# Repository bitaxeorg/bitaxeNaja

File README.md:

BitaxeNaja is a dual BM1373 Open Source Bitcoin miner using [esp-miner](https://github.com/skot/esp-miner)

The BM1373 used in this design is suspected to be the ASIC used in the Antminer S23 series miners.

It is still an untested prototype! Don't build this expecting it to work at all.

Bitaxe is an open source project released under the [CERN Open Hardware Licence Version 2 - Strongly Reciprocal](LICENSE)

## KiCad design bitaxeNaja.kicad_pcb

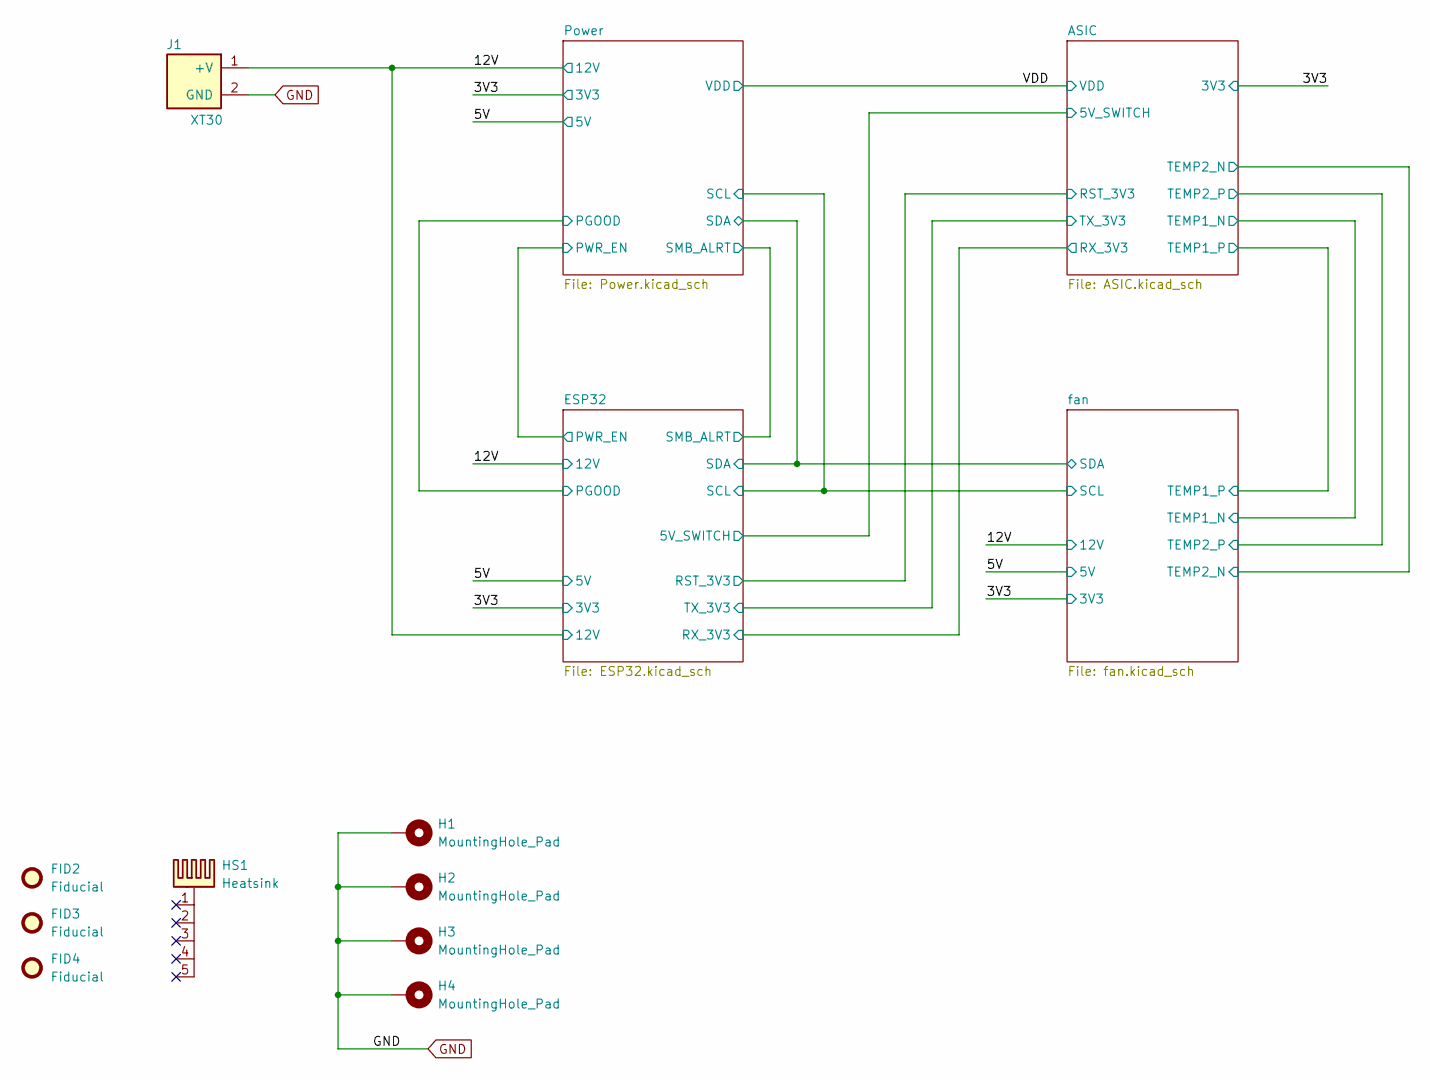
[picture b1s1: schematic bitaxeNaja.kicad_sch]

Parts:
FID2, FID3, FID4: Fiducial; Fiducial_1mm_Mask2mm
H1, H2, H3, H4: MountingHole_Pad; MountingHole_3.2mm_M3_Pad_Via
HS1: Heatsink; Heatsink-5hole-BitaxeGT
J1: XT30; XT30PW-M; PARTNO XT30PW-M; LCSC C431092

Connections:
/12V: J1.1 (+V); also elsewhere on the board
GND: H1.1 (1_1), H2.1 (1_1), H3.1 (1_1), H4.1 (1_1), J1.2 (GND); also elsewhere on the board

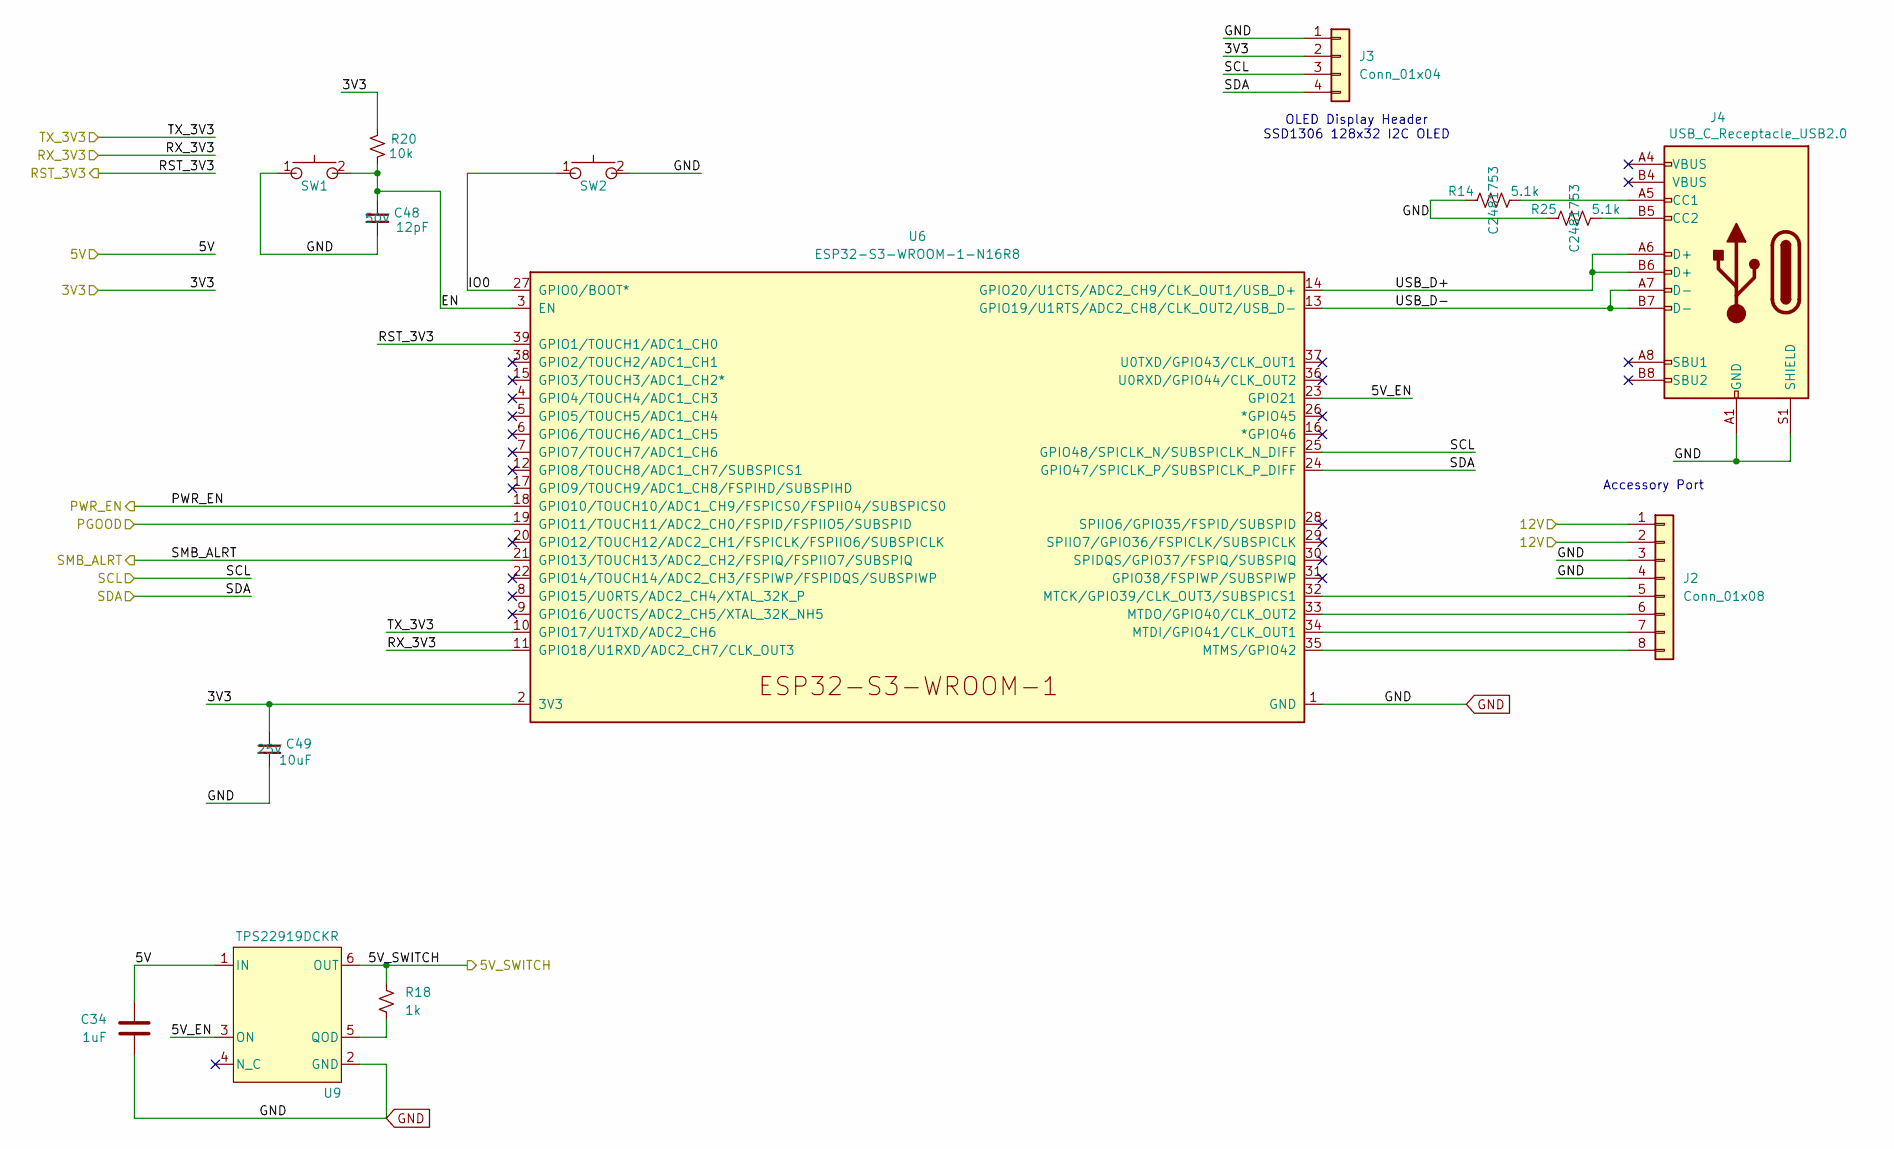
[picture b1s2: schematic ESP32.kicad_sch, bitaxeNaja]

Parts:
C34: 1uF; C_0402_1005Metric; PARTNO EMK105BJ105MV-F; LCSC C2177690
C48: 12pF; C_0402_1005Metric; Voltage 50V; PARTNO CC0402JRNPO9BN120
C49: 10uF; C_0603_1608Metric; Voltage 25V; PARTNO GRM188R61E106KA73D; LCSC C344022
J2: Conn_01x08; FPC-SMD_P0.50-8P_FGS-XJ-H2.0; PARTNO FFC2B35-08-T; LCSC C262657
J3: Conn_01x04; PinHeader_1x04_P2.54mm_Vertical_shifted
J4: USB_C_Receptacle_USB2.0; USB_C_Receptacle_GCT_USB4105-xx-A; PARTNO USB4105-GF-A
R14, R25: 5.1k; R_0402_1005Metric; PARTNO RMCF0402JT5K10; LCSC C2481753
R18: 1k; R_0402_1005Metric; PARTNO RC0402FR-071KL
R20: 10k; R_0402_1005Metric; PARTNO RC0402JR-0710KL; LCSC C25744
SW1, SW2: SWITCH-SPST; SW_TL3330AF130QG_EWI; PARTNO TL3330AF130QG
U6: ESP32-S3-WROOM-1-N16R8; ESP32-S3-WROOM-1; PARTNO ESP32-S3-WROOM-1-N16R8
U9: TPS22919DCKR; DCK0006A_N; PARTNO TPS22919DCKR

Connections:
/3V3: C49.1, J3.2, R20.2, U6.2 (3V3); also elsewhere on the board
/5V: C34.1, U9.1 (IN); also elsewhere on the board
/12V: J2.1, J2.2; also elsewhere on the board
/ASIC/5V_SWITCH: R18.1, U9.6 (OUT); also elsewhere on the board
/ASIC/RST_3V3: U6.39 (GPIO1/TOUCH1/ADC1_CH0); also elsewhere on the board
/ASIC/RX_3V3: U6.11 (GPIO18/U1RXD/ADC2_CH7/CLK_OUT3); also elsewhere on the board
/ASIC/TX_3V3: U6.10 (GPIO17/U1TXD/ADC2_CH6); also elsewhere on the board
/ESP32/5V_EN: U6.23 (GPIO21), U9.3 (ON)
/ESP32/EN: C48.1, R20.1, SW1.2, U6.3 (EN)
/ESP32/IO0: SW2.1, U6.27 (GPIO0/BOOT*)
/ESP32/PWR_EN: U6.18 (GPIO10/TOUCH10/ADC1_CH9/FSPICS0/FSPIIO4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); also elsewhere on the board
/ESP32/SCL: J3.3, U6.25 (GPIO48/SPICLK_N/SUBSPICLK_N_DIFF); also elsewhere on the board
/ESP32/SDA: J3.4, U6.24 (GPIO47/SPICLK_P/SUBSPICLK_P_DIFF); also elsewhere on the board
/ESP32/SMB_ALRT: U6.21 (GPIO13/TOUCH13/ADC2_CH2/FSPIQ/FSPIIO7/S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); also elsewhere on the board
/ESP32/USB_D+: J4.A6 (D+), J4.B6 (D+), U6.14 (GPIO20/U1CTS/ADC2_CH9/CLK_OUT1/USB_D+)
/ESP32/USB_D-: J4.A7 (D-), J4.B7 (D-), U6.13 (GPIO19/U1RTS/ADC2_CH8/CLK_OUT2/USB_D-)
/Power/PGOOD: U6.19 (GPIO11/TOUCH11/ADC2_CH0/FSPID/FSPIIO5/S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); also elsewhere on the board
GND: C34.2, C48.2, C49.2, J2.3, J2.4, J3.1, J4.A1 (GND), J4.B1 (GND), J4.S1 (SHIELD), R14.1, R25.1, SW1.1, SW2.2, U6.1 (GND), U6.40 (GND), U6.41 (GND), U9.2 (GND); also elsewhere on the board
unnamed: J2.5, U6.32 (MTCK/GPIO39/CLK_OUT3/SUBSPICS1)
unnamed: J2.6, U6.33 (MTDO/GPIO40/CLK_OUT2)
unnamed: J2.7, U6.34 (MTDI/GPIO41/CLK_OUT1)
unnamed: J2.8, U6.35 (MTMS/GPIO42)
unnamed: J4.A5 (CC1), R14.2
unnamed: J4.B5 (CC2), R25.2
unnamed: R18.2, U9.5 (QOD)

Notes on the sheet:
OLED Display Header SSD1306 128x32 I2C OLED
Accessory Port

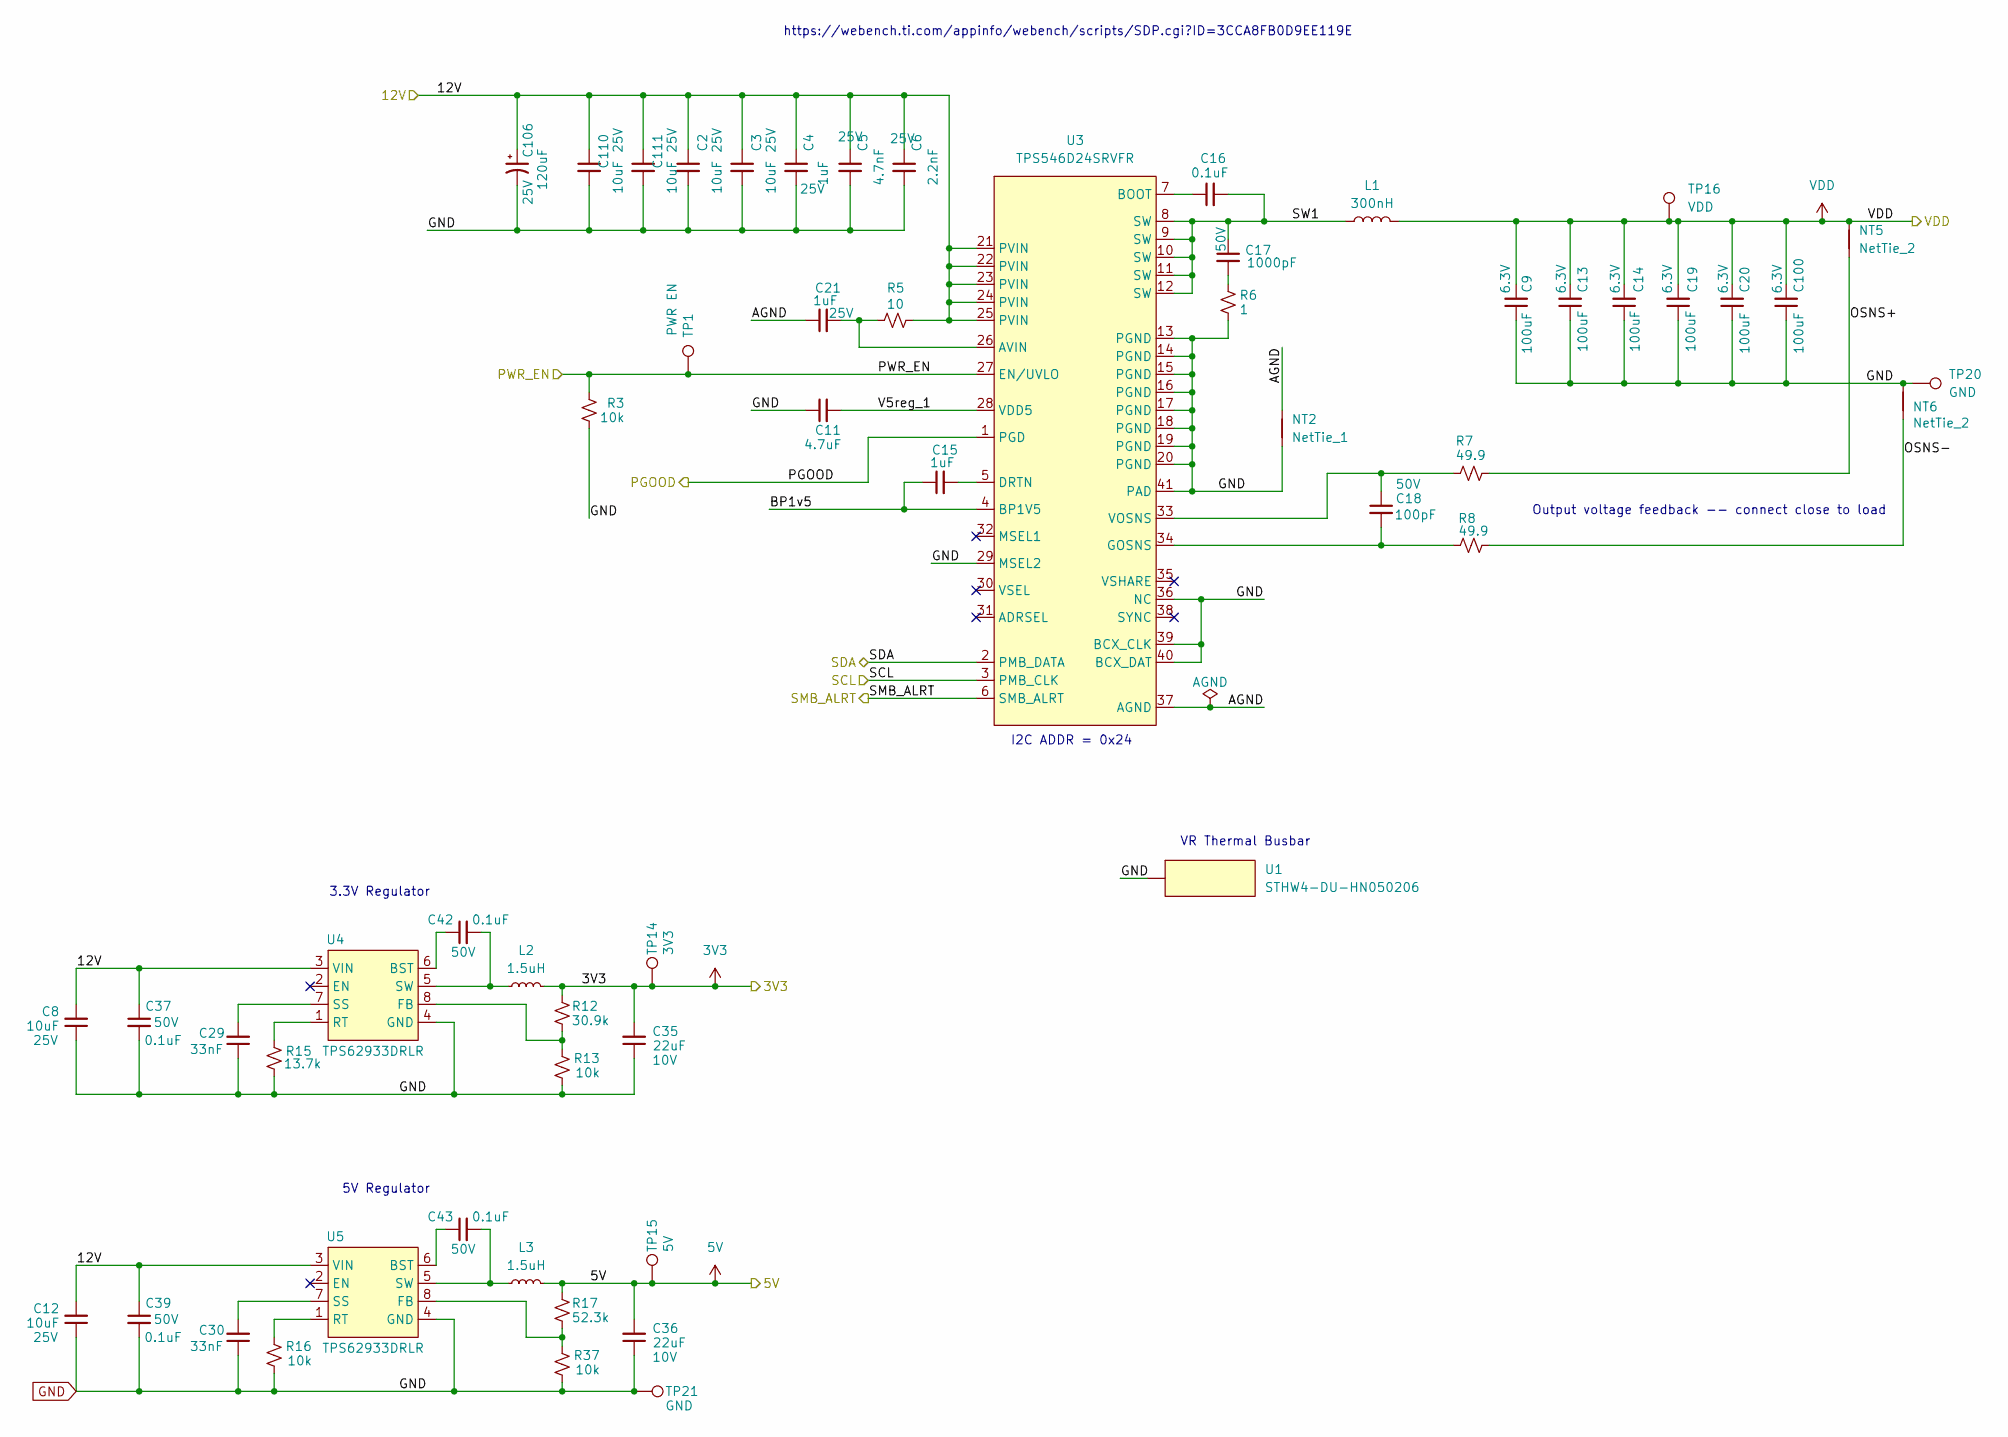
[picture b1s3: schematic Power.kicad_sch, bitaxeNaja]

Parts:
C2, C3, C8, C12, C110, C111: 10uF; C_0603_1608Metric; Voltage 25V; PARTNO GRM188R61E106KA73D; LCSC C344022
C4, C21: 1uF; C_0402_1005Metric; Voltage 25V; PARTNO TMK107B7105KA-T
C5: 4.7nF; C_0402_1005Metric; Voltage 25V; PARTNO GRM155R71E472KA01D
C6: 2.2nF; C_0402_1005Metric; Voltage 25V; PARTNO GRM155R61H222KA01D
C9, C13, C14, C19, C20, C100: 100uF; C_1206_3216Metric; Voltage 6.3V; PARTNO CL31A107MQHNNNE
C11: 4.7uF; C_0402_1005Metric; PARTNO GRM155R61A475MEAAD
C15: 1uF; C_0402_1005Metric; PARTNO EMK105BJ105MV-F; LCSC C2177690
C16, C37, C39, C42, C43: 0.1uF; C_0402_1005Metric; Voltage 50V; PARTNO GRM155R71H104KE14D; LCSC C77020
C17: 1000pF; C_0805_2012Metric; Voltage 50V; PARTNO CC0805KRX7R9BB102
C18: 100pF; C_0402_1005Metric; Voltage 50V; PARTNO CC0402JRNPO9BN101
C29, C30: 33nF; C_0402_1005Metric; PARTNO CC0402KRX7R9BB333; LCSC C106862
C35, C36: 22uF; C_0805_2012Metric; Voltage 10V; PARTNO CL21A226MPQNNNE; LCSC C29277
C106: 120uF; CP_Elec_6.3x5.9; Voltage 25V
L1: 300nH; SLC1175-271MEC_COC; PARTNO SLC1175-301
L2, L3: 1.5uH; IND-SMD_L2.0-W1.6; PARTNO FTC201612S1R5MBCA; LCSC C5832350
NT2: NetTie_1; NetTie-2_SMD_Pad0.2mmx1mm
NT5, NT6: NetTie_2; NetTie-2_SMD_Pad0.2mmx1mm
R3, R13, R16, R37: 10k; R_0402_1005Metric; PARTNO RC0402JR-0710KL; LCSC C25744
R5: 10; R_0402_1005Metric; PARTNO RC0402FR-0710RL
R6: 1; R_0805_2012Metric; PARTNO ESR10EZPJ1R0
R7, R8: 49.9; R_0402_1005Metric; PARTNO RC0402FR-0749R9L
R12: 30.9k; R_0402_1005Metric; PARTNO RC0402FR-0730K9L; LCSC C185428
R15: 13.7k; R_0402_1005Metric; PARTNO RC0402FR-0713K7L; LCSC C274888
R17: 52.3k; R_0402_1005Metric; PARTNO RC0402FR-0752K3L
TP1: PWR EN; TestPoint_Pad_D1.0mm
TP14: 3V3; TestPoint_Pad_D1.0mm
TP15: 5V; TestPoint_Pad_D1.0mm
TP16: VDD; TestPoint_Pad_D1.0mm
TP20: GND; TestPoint_Pad_D1.0mm
TP21: GND; TestPoint_Pad_D1.0mm; LCSC C138021
U1: STHW4-DU-HN050206; PAD-SMD_L5.0-W2.0_STHW4-DU-HN050206; LCSC C18548300
U3: TPS546D24SRVFR; LQFN40-CLIP; PARTNO TPS546D24SRVFR
U4, U5: TPS62933DRLR; SOT-583-8_L2.1-W1.2-P0.50-LS1.6-BR; PARTNO TPS62933DRLR; LCSC C3200405

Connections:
/3V3: C35.2, L2.2, R12.2, TP14.1 (1_1); also elsewhere on the board
/5V: C36.2, L3.2, R17.2, TP15.1 (1_1); also elsewhere on the board
/12V: C2.1, C3.1, C4.1, C5.1, C6.1, C8.2, C12.2, C37.1, C39.1, C106.1, C110.1, C111.1, R5.1, U3.21 (PVIN), U3.22 (PVIN), U3.23 (PVIN), U3.24 (PVIN), U3.25 (PVIN), U4.3 (VIN), U5.3 (VIN); also elsewhere on the board
/ESP32/PWR_EN: R3.2, TP1.1 (1_1), U3.27 (EN/UVLO); also elsewhere on the board
/ESP32/SCL: U3.3 (PMB_CLK); also elsewhere on the board
/ESP32/SDA: U3.2 (PMB_DATA); also elsewhere on the board
/ESP32/SMB_ALRT: U3.6 (SMB_ALRT); also elsewhere on the board
/Power/AGND: C21.1, NT2.2, U3.37 (AGND)
/Power/BP1v5: C15.1, U3.4 (BP1V5)
/Power/OSNS+: NT5.1, R7.1
/Power/OSNS-: NT6.1, R8.2
/Power/PGOOD: U3.1 (PGD); also elsewhere on the board
/Power/SW1: C16.2, C17.1, L1.1, U3.8 (SW), U3.9 (SW), U3.10 (SW), U3.11 (SW), U3.12 (SW)
/Power/V5reg_1: C11.2, U3.28 (VDD5)
/VDD: C9.2, C13.2, C14.2, C19.2, C20.2, C100.2, L1.2, NT5.2, TP16.1 (1_1); also elsewhere on the board
GND: C2.2, C3.2, C4.2, C5.2, C6.2, C8.1, C9.1, C11.1, C12.1, C13.1, C14.1, C19.1, C20.1, C29.1, C30.1, C35.1, C36.1, C37.2, C39.2, C100.1, C106.2, C110.2, C111.2, NT2.1, NT6.2, R3.1, R6.2, R13.1, R15.1, R16.1, R37.1, TP20.1 (1_1), TP21.1 (1_1), U1.1, U3.13 (PGND), U3.14 (PGND), U3.15 (PGND), U3.16 (PGND), U3.17 (PGND), U3.18 (PGND), U3.19 (PGND), U3.20 (PGND), U3.29 (MSEL2), U3.36 (NC), U3.39 (BCX_CLK), U3.40 (BCX_DAT), U3.41 (PAD), U4.4 (GND), U5.4 (GND); also elsewhere on the board
unnamed: C17.2, R6.1
unnamed: C21.2, R5.2, U3.26 (AVIN)
unnamed: C16.1, U3.7 (BOOT)
unnamed: C15.2, U3.5 (DRTN)
unnamed: C18.2, R8.1, U3.34 (GOSNS)
unnamed: C18.1, R7.2, U3.33 (VOSNS)
unnamed: C42.1, U4.6 (BST)
unnamed: R12.1, R13.2, U4.8 (FB)
unnamed: R15.2, U4.1 (RT)
unnamed: C29.2, U4.7 (SS)
unnamed: C42.2, L2.1, U4.5 (SW)
unnamed: C43.1, U5.6 (BST)
unnamed: R17.1, R37.2, U5.8 (FB)
unnamed: R16.2, U5.1 (RT)
unnamed: C30.2, U5.7 (SS)
unnamed: C43.2, L3.1, U5.5 (SW)

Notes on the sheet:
https://webench.ti.com/appinfo/webench/scripts/SDP.cgi?ID=3CCA8FB0D9EE119E
VR Thermal Busbar
I2C ADDR = 0x24
Output voltage feedback -- connect close to load
5V Regulator
3.3V Regulator

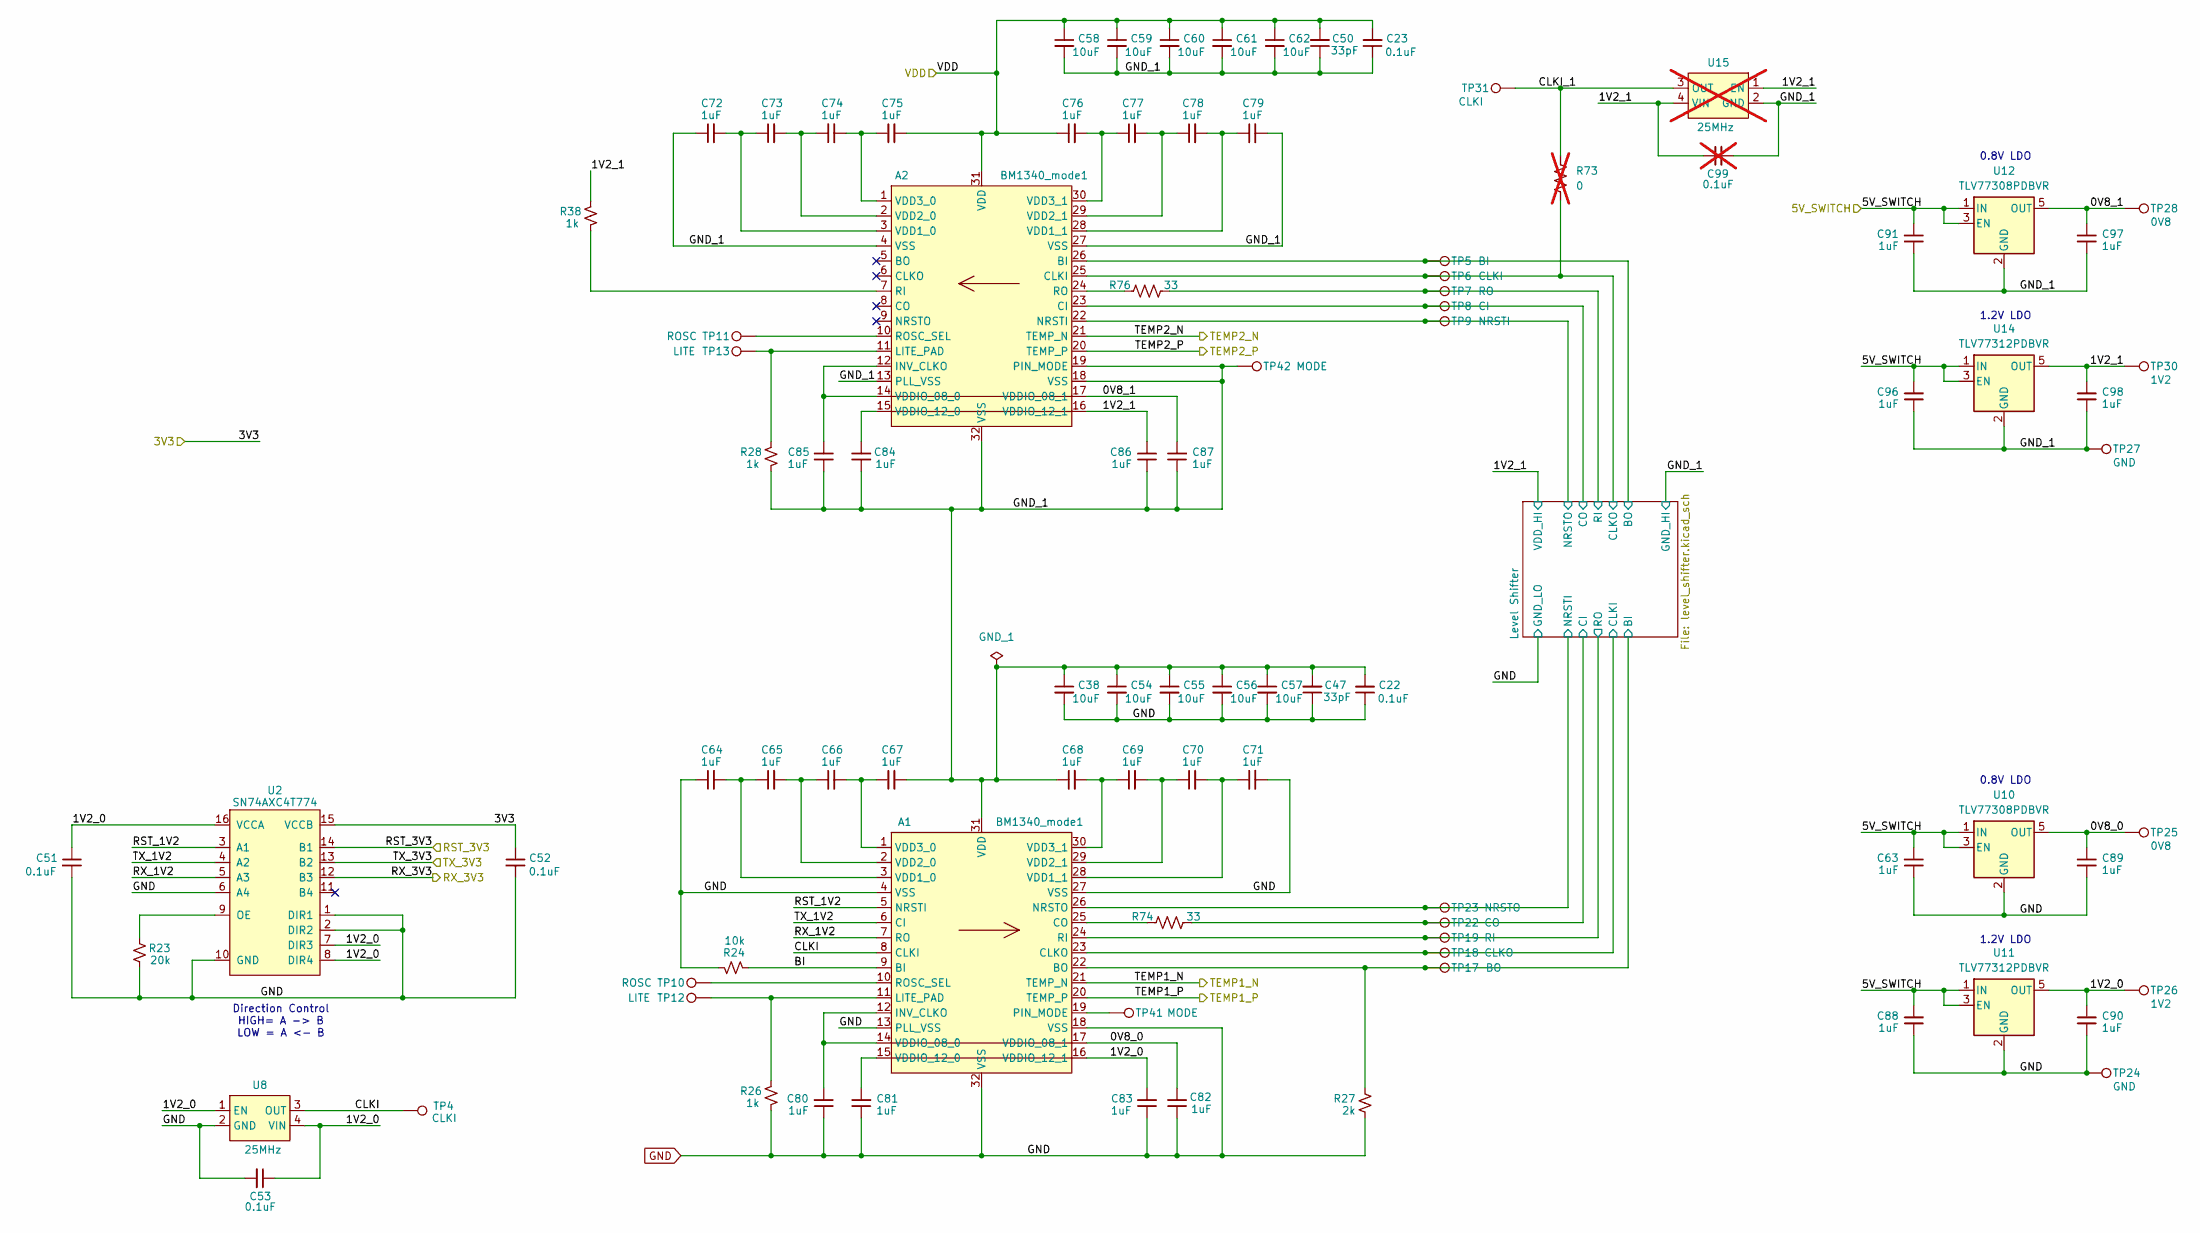
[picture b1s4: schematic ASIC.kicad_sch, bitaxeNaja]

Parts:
A1, A2: BM1340_mode1; BM1340
C22, C23: 0.1uF; C_0402_1005Metric; PARTNO GRM155R71H104KE14D; LCSC C77020
C38, C54, C55, C56, C57, C58, C59, C60, C61, C62: 10uF; C_0603_1608Metric; Voltage 25V; PARTNO GRM188R61E106KA73D; LCSC C344022
C47, C50: 33pF; C_0402_1005Metric; Voltage 25V; PARTNO KGM05ACG1E330JH
C51, C52, C53: 0.1uF; C_0402_1005Metric; PARTNO KGM05AR71C104KH
C63, C64, C65, C66, C67, C68, C69, C70, C71, C72, C73, C74, C75, C76, C77, C78, C79, C80, C81, C82, C83, C84, C85, C86, C87, C88, C89, C90, C91, C96, C97, C98: 1uF; C_0402_1005Metric; PARTNO EMK105BJ105MV-F; LCSC C2177690
C99: 0.1uF; C_0402_1005Metric; PARTNO KGM05AR71C104KH; not fitted
R23: 20k; R_0402_1005Metric; PARTNO RC0402FR-0720KL
R24: 10k; R_0402_1005Metric; PARTNO RC0402JR-0710KL; LCSC C25744
R26, R28, R38: 1k; R_0402_1005Metric; PARTNO RC0402FR-071KL
R27: 2k; R_0402_1005Metric; PARTNO RT0402BRD072KL
R73: 0; R_0402_1005Metric; PARTNO RC0402JR-070RL; not fitted
R74, R76: 33; R_0402_1005Metric
TP4, TP31: CLKI; TestPoint_Pad_D1.0mm
TP5: BI; TestPoint_Pad_1.0x0.4mm
TP6: CLKI; TestPoint_Pad_1.0x0.4mm
TP7: RO; TestPoint_Pad_1.0x0.4mm
TP8: CI; TestPoint_Pad_1.0x0.4mm
TP9: NRSTI; TestPoint_Pad_1.0x0.4mm
TP10, TP11: ROSC; TestPoint_Pad_1.0x0.4mm
TP12, TP13: LITE; TestPoint_Pad_1.0x0.4mm
TP17: BO; TestPoint_Pad_1.0x0.4mm
TP18: CLKO; TestPoint_Pad_1.0x0.4mm
TP19: RI; TestPoint_Pad_1.0x0.4mm
TP22: CO; TestPoint_Pad_1.0x0.4mm
TP23: NRSTO; TestPoint_Pad_1.0x0.4mm
TP24, TP27: GND; TestPoint_Pad_D1.0mm
TP25, TP28: 0V8; TestPoint_Pad_D1.0mm
TP26, TP30: 1V2; TestPoint_Pad_D1.0mm
TP41, TP42: MODE; TestPoint_Pad_1.0x0.4mm
U2: SN74AXC4T774; TSSOP-16_4.4x5mm_P0.65mm; PARTNO SN74AXC4T774PWR; LCSC C1849453
U8: 25MHz; SMD3225-4P; PARTNO SX3M25.000E20F30THN; LCSC C5137262
U10, U12: TLV77308PDBVR; SOT-23-5; PARTNO TLV77308PDBVR
U11, U14: TLV77312PDBVR; SOT-23-5; PARTNO TLV77312PDBVR
U15: 25MHz; SMD3225-4P; PARTNO SX3M25.000E20F30THN; LCSC C5137262; not fitted

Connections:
/3V3: C52.1, U2.15 (VCCB); also elsewhere on the board
/ASIC/5V_SWITCH: C63.2, C88.2, C91.2, C96.2, U10.1 (IN), U10.3 (EN), U11.1 (IN), U11.3 (EN), U12.1 (IN), U12.3 (EN), U14.1 (IN), U14.3 (EN); also elsewhere on the board
/ASIC/BI: A1.9 (BI), R24.2
/ASIC/CLKI: A1.8 (CLKI), TP4.1 (1_1), U8.3 (OUT)
/ASIC/CLKI_1: R73.2, TP31.1 (1_1), U15.3 (OUT)
/ASIC/GND_1: A1.31 (VDD), A2.4 (VSS), A2.13 (PLL_VSS), A2.18 (VSS), A2.19 (PIN_MODE), A2.27 (VSS), A2.32 (VSS), C22.2, C23.1, C38.1, C47.2, C50.1, C54.1, C55.1, C56.1, C57.1, C58.2, C59.2, C60.2, C61.2, C62.2, C67.2, C68.1, C72.1, C79.2, C84.1, C85.1, C86.1, C87.1, C91.1, C96.1, C97.1, C98.1, C99.2, R28.1, TP27.1 (1_1), TP42.1 (1_1), U12.2 (GND), U14.2 (GND), U15.2 (GND); also elsewhere on the board
/ASIC/Level Shifter/BI: A1.22 (BO), R27.2, TP17.1 (1_1); also elsewhere on the board
/ASIC/Level Shifter/BO: A2.26 (BI), TP5.1 (1_1); also elsewhere on the board
/ASIC/Level Shifter/CI: R74.2, TP22.1 (1_1); also elsewhere on the board
/ASIC/Level Shifter/CLKI: A1.23 (CLKO), TP18.1 (1_1); also elsewhere on the board
/ASIC/Level Shifter/CLKO: A2.25 (CLKI), R73.1, TP6.1 (1_1); also elsewhere on the board
/ASIC/Level Shifter/CO: A2.23 (CI), TP8.1 (1_1); also elsewhere on the board
/ASIC/Level Shifter/NRSTI: A1.26 (NRSTO), TP23.1 (1_1); also elsewhere on the board
/ASIC/Level Shifter/NRSTO: A2.22 (NRSTI), TP9.1 (1_1); also elsewhere on the board
/ASIC/Level Shifter/RI: R76.2, TP7.1 (1_1); also elsewhere on the board
/ASIC/Level Shifter/RO: A1.24 (RI), TP19.1 (1_1); also elsewhere on the board
/ASIC/RST_1V2: A1.5 (NRSTI), U2.3 (A1)
/ASIC/RST_3V3: U2.14 (B1); also elsewhere on the board
/ASIC/RX_1V2: A1.7 (RO), U2.5 (A3)
/ASIC/RX_3V3: U2.12 (B3); also elsewhere on the board
/ASIC/TEMP1_N: A1.21 (TEMP_N); also elsewhere on the board
/ASIC/TEMP1_P: A1.20 (TEMP_P); also elsewhere on the board
/ASIC/TEMP2_N: A2.21 (TEMP_N); also elsewhere on the board
/ASIC/TEMP2_P: A2.20 (TEMP_P); also elsewhere on the board
/ASIC/TX_1V2: A1.6 (CI), U2.4 (A2)
/ASIC/TX_3V3: U2.13 (B2); also elsewhere on the board
/VDD: A2.31 (VDD), C23.2, C50.2, C58.1, C59.1, C60.1, C61.1, C62.1, C75.2, C76.1; also elsewhere on the board
GND: A1.4 (VSS), A1.13 (PLL_VSS), A1.18 (VSS), A1.27 (VSS), A1.32 (VSS), C22.1, C38.2, C47.1, C51.2, C52.2, C53.2, C54.2, C55.2, C56.2, C57.2, C63.1, C64.1, C71.2, C80.1, C81.1, C82.1, C83.1, C88.1, C89.1, C90.1, R23.1, R24.1, R26.1, R27.1, TP24.1 (1_1), U2.1 (DIR1), U2.2 (DIR2), U2.6 (A4), U2.10 (GND), U8.2 (GND), U10.2 (GND), U11.2 (GND); also elsewhere on the board
unnamed: A1.25 (CO), R74.1
unnamed: A1.11 (LITE_PAD), R26.2, TP12.1 (1_1)
unnamed: A1.19 (PIN_MODE), TP41.1 (1_1)
unnamed: A1.10 (ROSC_SEL), TP10.1 (1_1)
unnamed: A1.3 (VDD1_0), C64.2, C65.1
unnamed: A1.28 (VDD1_1), C70.2, C71.1
unnamed: A1.2 (VDD2_0), C65.2, C66.1
unnamed: A1.29 (VDD2_1), C69.2, C70.1
unnamed: A1.1 (VDD3_0), C66.2, C67.1
unnamed: A1.30 (VDD3_1), C68.2, C69.1
unnamed: A2.11 (LITE_PAD), R28.2, TP13.1 (1_1)
unnamed: A2.7 (RI), R38.1
unnamed: A2.24 (RO), R76.1
unnamed: A2.10 (ROSC_SEL), TP11.1 (1_1)
unnamed: A2.3 (VDD1_0), C72.2, C73.1
unnamed: A2.28 (VDD1_1), C78.2, C79.1
unnamed: A2.2 (VDD2_0), C73.2, C74.1
unnamed: A2.29 (VDD2_1), C77.2, C78.1
unnamed: A2.1 (VDD3_0), C74.2, C75.1
unnamed: A2.30 (VDD3_1), C76.2, C77.1
unnamed: R23.2, U2.9 (OE)

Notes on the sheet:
0.8V LDO
1.2V LDO
Direction Control HIGH= A -> B LOW = A <- B

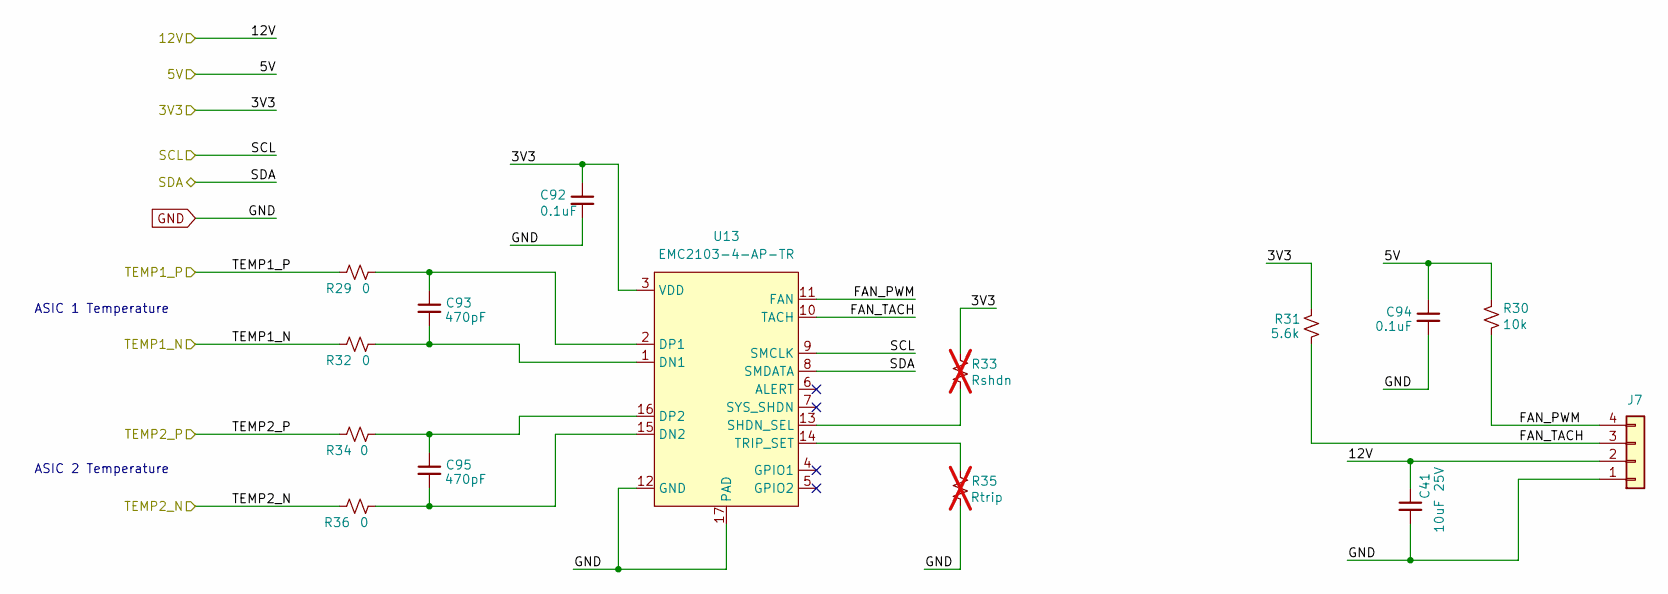
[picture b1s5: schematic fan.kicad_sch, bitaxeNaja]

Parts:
C41: 10uF; C_0603_1608Metric; Voltage 25V; PARTNO GRM188R61E106KA73D; LCSC C344022
C92, C94: 0.1uF; C_0402_1005Metric; PARTNO KGM05AR71C104KH
C93, C95: 470pF; C_0402_1005Metric; PARTNO GRM1555C1H471JA01D
J7: Conn_01x04; 470531000; PARTNO 0470531000
R29, R32, R34, R36: 0; R_0402_1005Metric; PARTNO RC0402JR-070RL
R30: 10k; R_0402_1005Metric; PARTNO RC0402JR-0710KL; LCSC C25744
R31: 5.6k; R_0402_1005Metric; PARTNO RC0402FR-075K6L
R33: Rshdn; R_0402_1005Metric; not fitted
R35: Rtrip; R_0402_1005Metric; not fitted
U13: EMC2103-4-AP-TR; QFN-16-1EP_4x4mm_P0.65mm_EP2.1x2.1mm; PARTNO EMC2103-4-AP-TR

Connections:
/3V3: C92.1, R31.2, R33.2, U13.3 (VDD); also elsewhere on the board
/5V: C94.1, R30.2; also elsewhere on the board
/12V: C41.1, J7.2; also elsewhere on the board
/ASIC/TEMP1_N: R32.2; also elsewhere on the board
/ASIC/TEMP1_P: R29.2; also elsewhere on the board
/ASIC/TEMP2_N: R36.2; also elsewhere on the board
/ASIC/TEMP2_P: R34.2; also elsewhere on the board
/ESP32/SCL: U13.9 (SMCLK); also elsewhere on the board
/ESP32/SDA: U13.8 (SMDATA); also elsewhere on the board
/fan/FAN_PWM: J7.4, R30.1, U13.11 (FAN)
/fan/FAN_TACH: J7.3, R31.1, U13.10 (TACH)
GND: C41.2, C92.2, C94.2, J7.1, R35.1, U13.12 (GND), U13.17 (PAD); also elsewhere on the board
unnamed: C93.2, R32.1, U13.1 (DN1)
unnamed: C95.2, R36.1, U13.15 (DN2)
unnamed: C93.1, R29.1, U13.2 (DP1)
unnamed: C95.1, R34.1, U13.16 (DP2)
unnamed: R33.1, U13.13 (SHDN_SEL)
unnamed: R35.2, U13.14 (TRIP_SET)

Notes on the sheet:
ASIC 2 Temperature
ASIC 1 Temperature

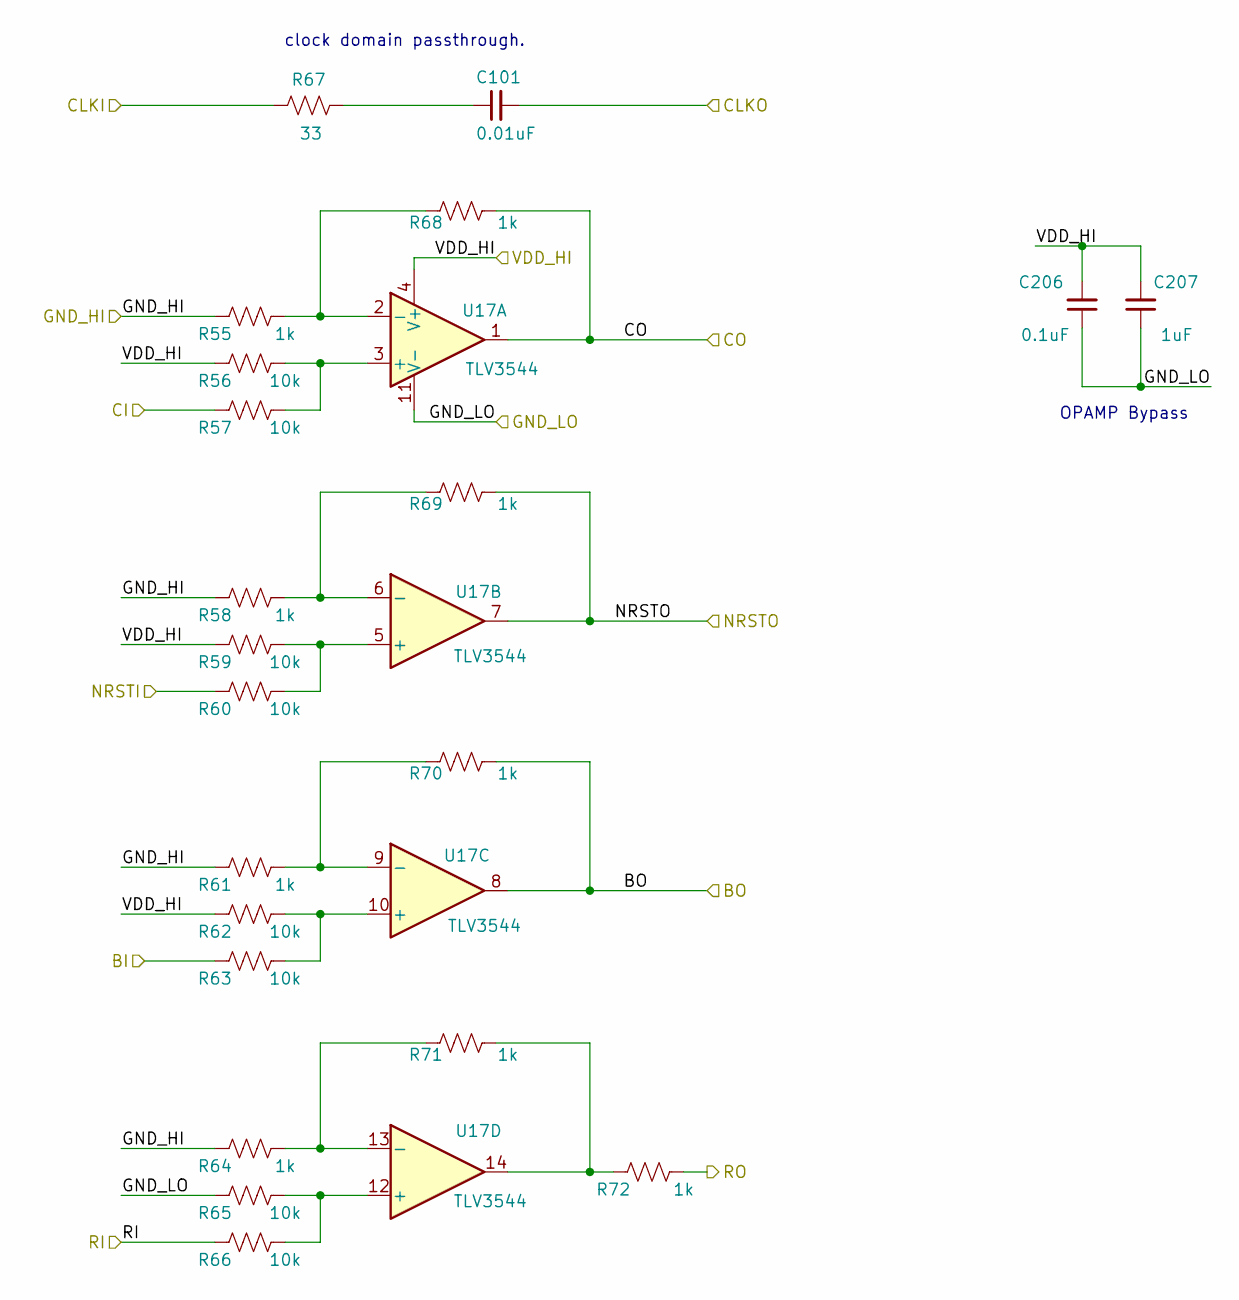
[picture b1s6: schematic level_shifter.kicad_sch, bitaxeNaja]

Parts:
C101: 0.01uF; C_0402_1005Metric
C206: 0.1uF; C_0402_1005Metric; PARTNO KGM05AR71C104KH
C207: 1uF; C_0402_1005Metric; PARTNO EMK105BJ105MV-F; LCSC C2177690
R55, R58, R61, R64, R68, R69, R70, R71, R72: 1k; R_0402_1005Metric; PARTNO RC0402FR-071KL
R56, R57, R59, R60, R62, R63, R65, R66: 10k; R_0402_1005Metric; PARTNO RC0402JR-0710KL; LCSC C25744
R67: 33; R_0402_1005Metric
U17: TLV3544; TSSOP-14_4.4x5mm_P0.65mm; PARTNO TLV3544IPWR

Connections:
/ASIC/GND_1: R55.2, R58.2, R61.2, R64.2; also elsewhere on the board
/ASIC/Level Shifter/BI: R63.1; also elsewhere on the board
/ASIC/Level Shifter/BO: R70.1, U17.8; also elsewhere on the board
/ASIC/Level Shifter/CI: R57.1; also elsewhere on the board
/ASIC/Level Shifter/CLKI: R67.1; also elsewhere on the board
/ASIC/Level Shifter/CLKO: C101.2; also elsewhere on the board
/ASIC/Level Shifter/CO: R68.1, U17.1; also elsewhere on the board
/ASIC/Level Shifter/NRSTI: R60.1; also elsewhere on the board
/ASIC/Level Shifter/NRSTO: R69.1, U17.7; also elsewhere on the board
/ASIC/Level Shifter/RI: R66.1; also elsewhere on the board
/ASIC/Level Shifter/RO: R72.1; also elsewhere on the board
GND: C206.1, C207.1, R65.1, U17.11 (V-); also elsewhere on the board
unnamed: C101.1, R67.2
unnamed: R71.1, R72.2, U17.14
unnamed: R56.1, R57.2, U17.3 (+)
unnamed: R55.1, R68.2, U17.2 (-)
unnamed: R59.2, R60.2, U17.5 (+)
unnamed: R58.1, R69.2, U17.6 (-)
unnamed: R62.2, R63.2, U17.10 (+)
unnamed: R61.1, R70.2, U17.9 (-)
unnamed: R65.2, R66.2, U17.12 (+)
unnamed: R64.1, R71.2, U17.13 (-)

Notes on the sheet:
OPAMP Bypass
clock domain passthrough.

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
